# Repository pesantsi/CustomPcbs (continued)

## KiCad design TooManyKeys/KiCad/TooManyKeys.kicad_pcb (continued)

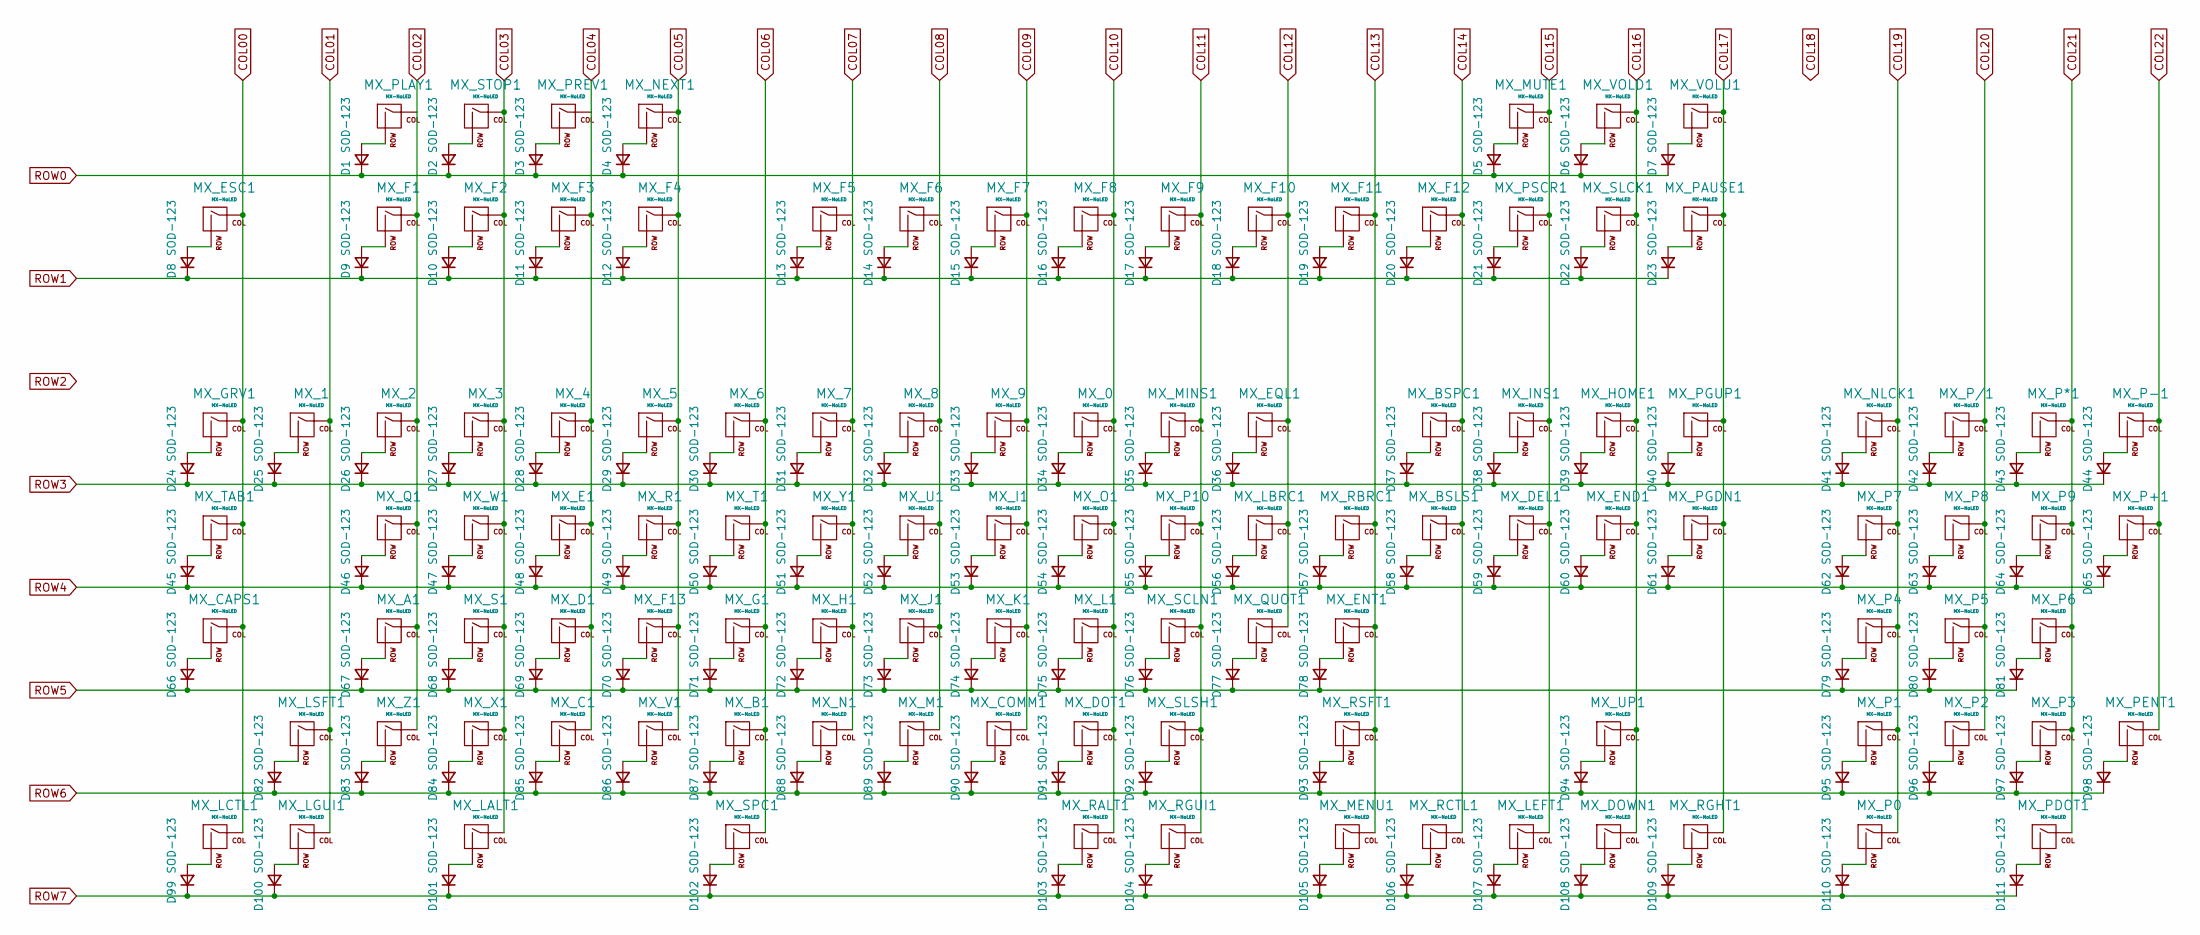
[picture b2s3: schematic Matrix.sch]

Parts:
D1, D2, D3, D4, D5, D6, D7, D8, D9, D10, D11, D12, D13, D14, D15, D16, D17, D18, D19, D20, D21, D22, D23, D24, D25, D26, D27, D28, D29, D30, D31, D32, D33, D34, D35, D36, D37, D38, D39, D40, D41, D42, D43, D44, D45, D46, D47, D48, D49, D50, D51, D52, D53, D54, D55, D56, D57, D58, D59, D60, D61, D62, D63, D64, D65, D66, D67, D68, D69, D70, D71, D72, D73, D74, D75, D76, D77, D78, D79, D80, D81, D82, D83, D84, D85, D86, D87, D88, D89, D90, D91, D92, D93, D94, D95, D96, D97, D98, D99, D100, D101, D102, D103, D104, D105, D106, D107, D108, D109, D110, D111: SOD-123; D_SOD-123
MX_0, MX_1, MX_2, MX_3, MX_4, MX_5, MX_6, MX_7, MX_8, MX_9: MX-NoLED; MXOnly-1U-NoLED
MX_A1: MX-NoLED; MXOnly-1U-NoLED
MX_B1: MX-NoLED; MXOnly-1U-NoLED
MX_BSLS1: MX-NoLED; MXOnly-1.5U-NoLED
MX_BSPC1: MX-NoLED; MXOnly-2U-NoLED
MX_C1: MX-NoLED; MXOnly-1U-NoLED
MX_CAPS1: MX-NoLED; MXOnly-1.75U-NoLED
MX_COMM1: MX-NoLED; MXOnly-1U-NoLED
MX_D1: MX-NoLED; MXOnly-1U-NoLED
MX_DEL1: MX-NoLED; MXOnly-1U-NoLED
MX_DOT1: MX-NoLED; MXOnly-1U-NoLED
MX_DOWN1: MX-NoLED; MXOnly-1U-NoLED
MX_E1: MX-NoLED; MXOnly-1U-NoLED
MX_END1: MX-NoLED; MXOnly-1U-NoLED
MX_ENT1: MX-NoLED; MXOnly-2.25U-NoLED
MX_EQL1: MX-NoLED; MXOnly-1U-NoLED
MX_ESC1: MX-NoLED; MXOnly-1U-NoLED
MX_F1, MX_F2, MX_F3, MX_F4, MX_F5, MX_F6, MX_F7, MX_F8, MX_F9, MX_F10, MX_F11, MX_F12, MX_F13: MX-NoLED; MXOnly-1U-NoLED
MX_G1: MX-NoLED; MXOnly-1U-NoLED
MX_GRV1: MX-NoLED; MXOnly-1U-NoLED
MX_H1: MX-NoLED; MXOnly-1U-NoLED
MX_HOME1: MX-NoLED; MXOnly-1U-NoLED
MX_I1: MX-NoLED; MXOnly-1U-NoLED
MX_INS1: MX-NoLED; MXOnly-1U-NoLED
MX_J1: MX-NoLED; MXOnly-1U-NoLED
MX_K1: MX-NoLED; MXOnly-1U-NoLED
MX_L1: MX-NoLED; MXOnly-1U-NoLED
MX_LALT1: MX-NoLED; MXOnly-1.25U-NoLED
MX_LBRC1: MX-NoLED; MXOnly-1U-NoLED
MX_LCTL1: MX-NoLED; MXOnly-1.25U-NoLED
MX_LEFT1: MX-NoLED; MXOnly-1U-NoLED
MX_LGUI1: MX-NoLED; MXOnly-1.25U-NoLED
MX_LSFT1: MX-NoLED; MXOnly-2.25U-NoLED
MX_M1: MX-NoLED; MXOnly-1U-NoLED
MX_MENU1: MX-NoLED; MXOnly-1.25U-NoLED
MX_MINS1: MX-NoLED; MXOnly-1U-NoLED
MX_MUTE1: MX-NoLED; MXOnly-1U-NoLED
MX_N1: MX-NoLED; MXOnly-1U-NoLED
MX_NEXT1: MX-NoLED; MXOnly-1U-NoLED
MX_NLCK1: MX-NoLED; MXOnly-1U-NoLED
MX_O1: MX-NoLED; MXOnly-1U-NoLED
MX_P0: MX-NoLED; MXOnly-2U-NoLED
MX_P1, MX_P2, MX_P3, MX_P4, MX_P5, MX_P6, MX_P7, MX_P8, MX_P9, MX_P10: MX-NoLED; MXOnly-1U-NoLED
MX_P*1: MX-NoLED; MXOnly-1U-NoLED
MX_P+1: MX-NoLED; MXOnly-2U-NoLED_Vertical
MX_P-1: MX-NoLED; MXOnly-1U-NoLED
MX_P/1: MX-NoLED; MXOnly-1U-NoLED
MX_PAUSE1: MX-NoLED; MXOnly-1U-NoLED
MX_PDOT1: MX-NoLED; MXOnly-1U-NoLED
MX_PENT1: MX-NoLED; MXOnly-2U-NoLED_Vertical
MX_PGDN1: MX-NoLED; MXOnly-1U-NoLED
MX_PGUP1: MX-NoLED; MXOnly-1U-NoLED
MX_PLAY1: MX-NoLED; MXOnly-1U-NoLED
MX_PREV1: MX-NoLED; MXOnly-1U-NoLED
MX_PSCR1: MX-NoLED; MXOnly-1U-NoLED
MX_Q1: MX-NoLED; MXOnly-1U-NoLED
MX_QUOT1: MX-NoLED; MXOnly-1U-NoLED
MX_R1: MX-NoLED; MXOnly-1U-NoLED
MX_RALT1: MX-NoLED; MXOnly-1.25U-NoLED
MX_RBRC1: MX-NoLED; MXOnly-1U-NoLED
MX_RCTL1: MX-NoLED; MXOnly-1.25U-NoLED
MX_RGHT1: MX-NoLED; MXOnly-1U-NoLED
MX_RGUI1: MX-NoLED; MXOnly-1.25U-NoLED
MX_RSFT1: MX-NoLED; MXOnly-2.75U-NoLED
MX_S1: MX-NoLED; MXOnly-1U-NoLED
MX_SCLN1: MX-NoLED; MXOnly-1U-NoLED
MX_SLCK1: MX-NoLED; MXOnly-1U-NoLED
MX_SLSH1: MX-NoLED; MXOnly-1U-NoLED
MX_SPC1: MX-NoLED; MXOnly-6.25U-NoLED
MX_STOP1: MX-NoLED; MXOnly-1U-NoLED
MX_T1: MX-NoLED; MXOnly-1U-NoLED
MX_TAB1: MX-NoLED; MXOnly-1.5U-NoLED
MX_U1: MX-NoLED; MXOnly-1U-NoLED
MX_UP1: MX-NoLED; MXOnly-1U-NoLED
MX_V1: MX-NoLED; MXOnly-1U-NoLED
MX_VOLD1: MX-NoLED; MXOnly-1U-NoLED
MX_VOLU1: MX-NoLED; MXOnly-1U-NoLED
MX_W1: MX-NoLED; MXOnly-1U-NoLED
MX_X1: MX-NoLED; MXOnly-1U-NoLED
MX_Y1: MX-NoLED; MXOnly-1U-NoLED
MX_Z1: MX-NoLED; MXOnly-1U-NoLED

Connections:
COL00: MX_CAPS1.1 (COL), MX_ESC1.1 (COL), MX_GRV1.1 (COL), MX_LCTL1.1 (COL), MX_TAB1.1 (COL); also elsewhere on the board
COL01: MX_1.1 (COL), MX_LGUI1.1 (COL), MX_LSFT1.1 (COL); also elsewhere on the board
COL02: MX_2.1 (COL), MX_A1.1 (COL), MX_F1.1 (COL), MX_PLAY1.1 (COL), MX_Q1.1 (COL), MX_Z1.1 (COL); also elsewhere on the board
COL03: MX_3.1 (COL), MX_F2.1 (COL), MX_LALT1.1 (COL), MX_S1.1 (COL), MX_STOP1.1 (COL), MX_W1.1 (COL), MX_X1.1 (COL); also elsewhere on the board
COL04: MX_4.1 (COL), MX_C1.1 (COL), MX_D1.1 (COL), MX_E1.1 (COL), MX_F3.1 (COL), MX_PREV1.1 (COL); also elsewhere on the board
COL05: MX_5.1 (COL), MX_F4.1 (COL), MX_F13.1 (COL), MX_NEXT1.1 (COL), MX_R1.1 (COL), MX_V1.1 (COL); also elsewhere on the board
COL06: MX_6.1 (COL), MX_B1.1 (COL), MX_G1.1 (COL), MX_SPC1.1 (COL), MX_T1.1 (COL); also elsewhere on the board
COL07: MX_7.1 (COL), MX_F5.1 (COL), MX_H1.1 (COL), MX_N1.1 (COL), MX_Y1.1 (COL); also elsewhere on the board
COL08: MX_8.1 (COL), MX_F6.1 (COL), MX_J1.1 (COL), MX_M1.1 (COL), MX_U1.1 (COL); also elsewhere on the board
COL09: MX_9.1 (COL), MX_COMM1.1 (COL), MX_F7.1 (COL), MX_I1.1 (COL), MX_K1.1 (COL); also elsewhere on the board
COL10: MX_0.1 (COL), MX_DOT1.1 (COL), MX_F8.1 (COL), MX_L1.1 (COL), MX_O1.1 (COL), MX_RALT1.1 (COL); also elsewhere on the board
COL11: MX_F9.1 (COL), MX_MINS1.1 (COL), MX_P10.1 (COL), MX_RGUI1.1 (COL), MX_SCLN1.1 (COL), MX_SLSH1.1 (COL); also elsewhere on the board
COL12: MX_EQL1.1 (COL), MX_F10.1 (COL), MX_LBRC1.1 (COL), MX_QUOT1.1 (COL); also elsewhere on the board
COL13: MX_ENT1.1 (COL), MX_F11.1 (COL), MX_MENU1.1 (COL), MX_RBRC1.1 (COL), MX_RSFT1.1 (COL); also elsewhere on the board
COL14: MX_BSLS1.1 (COL), MX_BSPC1.1 (COL), MX_F12.1 (COL), MX_RCTL1.1 (COL); also elsewhere on the board
COL15: MX_DEL1.1 (COL), MX_INS1.1 (COL), MX_LEFT1.1 (COL), MX_MUTE1.1 (COL), MX_PSCR1.1 (COL); also elsewhere on the board
COL16: MX_DOWN1.1 (COL), MX_END1.1 (COL), MX_HOME1.1 (COL), MX_SLCK1.1 (COL), MX_UP1.1 (COL), MX_VOLD1.1 (COL); also elsewhere on the board
COL17: MX_PAUSE1.1 (COL), MX_PGDN1.1 (COL), MX_PGUP1.1 (COL), MX_RGHT1.1 (COL), MX_VOLU1.1 (COL); also elsewhere on the board
COL19: MX_NLCK1.1 (COL), MX_P0.1 (COL), MX_P1.1 (COL), MX_P4.1 (COL), MX_P7.1 (COL); also elsewhere on the board
COL20: MX_P2.1 (COL), MX_P5.1 (COL), MX_P8.1 (COL), MX_P/1.1 (COL); also elsewhere on the board
COL21: MX_P3.1 (COL), MX_P6.1 (COL), MX_P9.1 (COL), MX_P*1.1 (COL), MX_PDOT1.1 (COL); also elsewhere on the board
COL22: MX_P+1.1 (COL), MX_P-1.1 (COL), MX_PENT1.1 (COL); also elsewhere on the board
unnamed: D1.2 (A), MX_PLAY1.2 (ROW)
unnamed: D2.2 (A), MX_STOP1.2 (ROW)
unnamed: D3.2 (A), MX_PREV1.2 (ROW)
unnamed: D4.2 (A), MX_NEXT1.2 (ROW)
unnamed: D5.2 (A), MX_MUTE1.2 (ROW)
unnamed: D6.2 (A), MX_VOLD1.2 (ROW)
unnamed: D7.2 (A), MX_VOLU1.2 (ROW)
unnamed: D8.2 (A), MX_ESC1.2 (ROW)
unnamed: D9.2 (A), MX_F1.2 (ROW)
unnamed: D10.2 (A), MX_F2.2 (ROW)
unnamed: D11.2 (A), MX_F3.2 (ROW)
unnamed: D12.2 (A), MX_F4.2 (ROW)
unnamed: D13.2 (A), MX_F5.2 (ROW)
unnamed: D14.2 (A), MX_F6.2 (ROW)
unnamed: D15.2 (A), MX_F7.2 (ROW)
unnamed: D16.2 (A), MX_F8.2 (ROW)
unnamed: D17.2 (A), MX_F9.2 (ROW)
unnamed: D18.2 (A), MX_F10.2 (ROW)
unnamed: D19.2 (A), MX_F11.2 (ROW)
unnamed: D20.2 (A), MX_F12.2 (ROW)
unnamed: D21.2 (A), MX_PSCR1.2 (ROW)
unnamed: D22.2 (A), MX_SLCK1.2 (ROW)
unnamed: D23.2 (A), MX_PAUSE1.2 (ROW)
unnamed: D24.2 (A), MX_GRV1.2 (ROW)
unnamed: D25.2 (A), MX_1.2 (ROW)
unnamed: D26.2 (A), MX_2.2 (ROW)
unnamed: D27.2 (A), MX_3.2 (ROW)
unnamed: D28.2 (A), MX_4.2 (ROW)
unnamed: D29.2 (A), MX_5.2 (ROW)
unnamed: D30.2 (A), MX_6.2 (ROW)
unnamed: D31.2 (A), MX_7.2 (ROW)
unnamed: D32.2 (A), MX_8.2 (ROW)
unnamed: D33.2 (A), MX_9.2 (ROW)
unnamed: D34.2 (A), MX_0.2 (ROW)
unnamed: D35.2 (A), MX_MINS1.2 (ROW)
unnamed: D36.2 (A), MX_EQL1.2 (ROW)
unnamed: D37.2 (A), MX_BSPC1.2 (ROW)
unnamed: D38.2 (A), MX_INS1.2 (ROW)
unnamed: D39.2 (A), MX_HOME1.2 (ROW)
unnamed: D40.2 (A), MX_PGUP1.2 (ROW)
unnamed: D41.2 (A), MX_NLCK1.2 (ROW)
unnamed: D42.2 (A), MX_P/1.2 (ROW)
unnamed: D43.2 (A), MX_P*1.2 (ROW)
unnamed: D44.2 (A), MX_P-1.2 (ROW)
unnamed: D45.2 (A), MX_TAB1.2 (ROW)
unnamed: D46.2 (A), MX_Q1.2 (ROW)
unnamed: D47.2 (A), MX_W1.2 (ROW)
unnamed: D48.2 (A), MX_E1.2 (ROW)
unnamed: D49.2 (A), MX_R1.2 (ROW)
unnamed: D50.2 (A), MX_T1.2 (ROW)
unnamed: D51.2 (A), MX_Y1.2 (ROW)
unnamed: D52.2 (A), MX_U1.2 (ROW)
unnamed: D53.2 (A), MX_I1.2 (ROW)
unnamed: D54.2 (A), MX_O1.2 (ROW)
unnamed: D55.2 (A), MX_P10.2 (ROW)
unnamed: D56.2 (A), MX_LBRC1.2 (ROW)
unnamed: D57.2 (A), MX_RBRC1.2 (ROW)
unnamed: D58.2 (A), MX_BSLS1.2 (ROW)
unnamed: D59.2 (A), MX_DEL1.2 (ROW)
unnamed: D60.2 (A), MX_END1.2 (ROW)
unnamed: D61.2 (A), MX_PGDN1.2 (ROW)
unnamed: D62.2 (A), MX_P7.2 (ROW)
unnamed: D63.2 (A), MX_P8.2 (ROW)
unnamed: D64.2 (A), MX_P9.2 (ROW)
unnamed: D65.2 (A), MX_P+1.2 (ROW)
unnamed: D66.2 (A), MX_CAPS1.2 (ROW)
unnamed: D67.2 (A), MX_A1.2 (ROW)
unnamed: D68.2 (A), MX_S1.2 (ROW)
unnamed: D69.2 (A), MX_D1.2 (ROW)
unnamed: D70.2 (A), MX_F13.2 (ROW)
unnamed: D71.2 (A), MX_G1.2 (ROW)
unnamed: D72.2 (A), MX_H1.2 (ROW)
unnamed: D73.2 (A), MX_J1.2 (ROW)
unnamed: D74.2 (A), MX_K1.2 (ROW)
unnamed: D75.2 (A), MX_L1.2 (ROW)
unnamed: D76.2 (A), MX_SCLN1.2 (ROW)
unnamed: D77.2 (A), MX_QUOT1.2 (ROW)
unnamed: D78.2 (A), MX_ENT1.2 (ROW)
unnamed: D79.2 (A), MX_P4.2 (ROW)
unnamed: D80.2 (A), MX_P5.2 (ROW)
unnamed: D81.2 (A), MX_P6.2 (ROW)
unnamed: D82.2 (A), MX_LSFT1.2 (ROW)
unnamed: D83.2 (A), MX_Z1.2 (ROW)
unnamed: D84.2 (A), MX_X1.2 (ROW)
unnamed: D85.2 (A), MX_C1.2 (ROW)
unnamed: D86.2 (A), MX_V1.2 (ROW)
unnamed: D87.2 (A), MX_B1.2 (ROW)
unnamed: D88.2 (A), MX_N1.2 (ROW)
unnamed: D89.2 (A), MX_M1.2 (ROW)
unnamed: D90.2 (A), MX_COMM1.2 (ROW)
unnamed: D91.2 (A), MX_DOT1.2 (ROW)
unnamed: D92.2 (A), MX_SLSH1.2 (ROW)
unnamed: D93.2 (A), MX_RSFT1.2 (ROW)
unnamed: D94.2 (A), MX_UP1.2 (ROW)
unnamed: D95.2 (A), MX_P1.2 (ROW)
unnamed: D96.2 (A), MX_P2.2 (ROW)
unnamed: D97.2 (A), MX_P3.2 (ROW)
unnamed: D98.2 (A), MX_PENT1.2 (ROW)
unnamed: D99.2 (A), MX_LCTL1.2 (ROW)
unnamed: D100.2 (A), MX_LGUI1.2 (ROW)
unnamed: D101.2 (A), MX_LALT1.2 (ROW)
unnamed: D102.2 (A), MX_SPC1.2 (ROW)
unnamed: D103.2 (A), MX_RALT1.2 (ROW)
unnamed: D104.2 (A), MX_RGUI1.2 (ROW)
unnamed: D105.2 (A), MX_MENU1.2 (ROW)
unnamed: D106.2 (A), MX_RCTL1.2 (ROW)
unnamed: D107.2 (A), MX_LEFT1.2 (ROW)
unnamed: D108.2 (A), MX_DOWN1.2 (ROW)
unnamed: D109.2 (A), MX_RGHT1.2 (ROW)
unnamed: D110.2 (A), MX_P0.2 (ROW)
unnamed: D111.2 (A), MX_PDOT1.2 (ROW)
ROW0: D1.1 (K), D2.1 (K), D3.1 (K), D4.1 (K), D5.1 (K), D6.1 (K), D7.1 (K); also elsewhere on the board
ROW1: D8.1 (K), D9.1 (K), D10.1 (K), D11.1 (K), D12.1 (K), D13.1 (K), D14.1 (K), D15.1 (K), D16.1 (K), D17.1 (K), D18.1 (K), D19.1 (K), D20.1 (K), D21.1 (K), D22.1 (K), D23.1 (K); also elsewhere on the board
ROW3: D24.1 (K), D25.1 (K), D26.1 (K), D27.1 (K), D28.1 (K), D29.1 (K), D30.1 (K), D31.1 (K), D32.1 (K), D33.1 (K), D34.1 (K), D35.1 (K), D36.1 (K), D37.1 (K), D38.1 (K), D39.1 (K), D40.1 (K), D41.1 (K), D42.1 (K), D43.1 (K), D44.1 (K); also elsewhere on the board
ROW4: D45.1 (K), D46.1 (K), D47.1 (K), D48.1 (K), D49.1 (K), D50.1 (K), D51.1 (K), D52.1 (K), D53.1 (K), D54.1 (K), D55.1 (K), D56.1 (K), D57.1 (K), D58.1 (K), D59.1 (K), D60.1 (K), D61.1 (K), D62.1 (K), D63.1 (K), D64.1 (K), D65.1 (K); also elsewhere on the board
ROW5: D66.1 (K), D67.1 (K), D68.1 (K), D69.1 (K), D70.1 (K), D71.1 (K), D72.1 (K), D73.1 (K), D74.1 (K), D75.1 (K), D76.1 (K), D77.1 (K), D78.1 (K), D79.1 (K), D80.1 (K), D81.1 (K); also elsewhere on the board
ROW6: D82.1 (K), D83.1 (K), D84.1 (K), D85.1 (K), D86.1 (K), D87.1 (K), D88.1 (K), D89.1 (K), D90.1 (K), D91.1 (K), D92.1 (K), D93.1 (K), D94.1 (K), D95.1 (K), D96.1 (K), D97.1 (K), D98.1 (K); also elsewhere on the board
ROW7: D99.1 (K), D100.1 (K), D101.1 (K), D102.1 (K), D103.1 (K), D104.1 (K), D105.1 (K), D106.1 (K), D107.1 (K), D108.1 (K), D109.1 (K), D110.1 (K), D111.1 (K); also elsewhere on the board

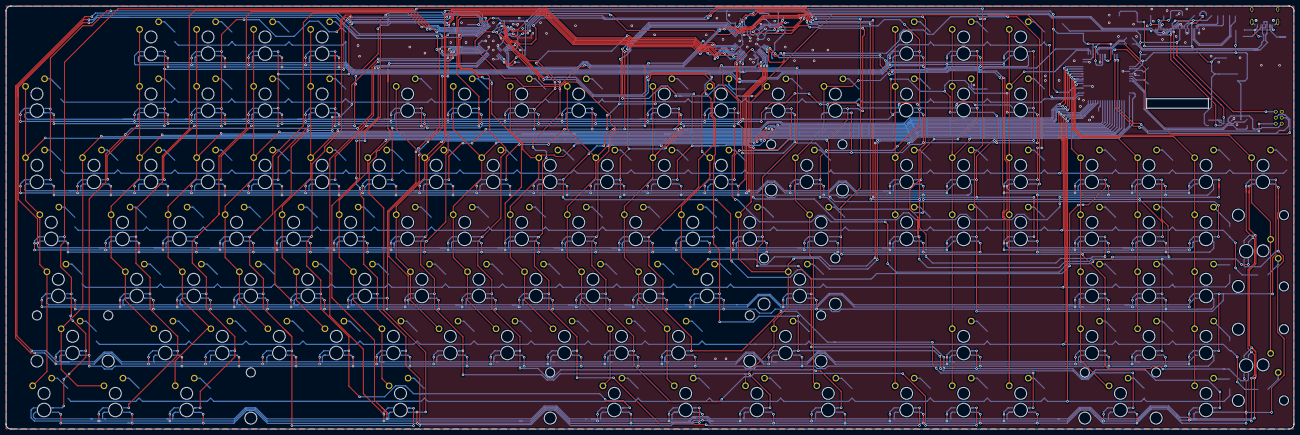
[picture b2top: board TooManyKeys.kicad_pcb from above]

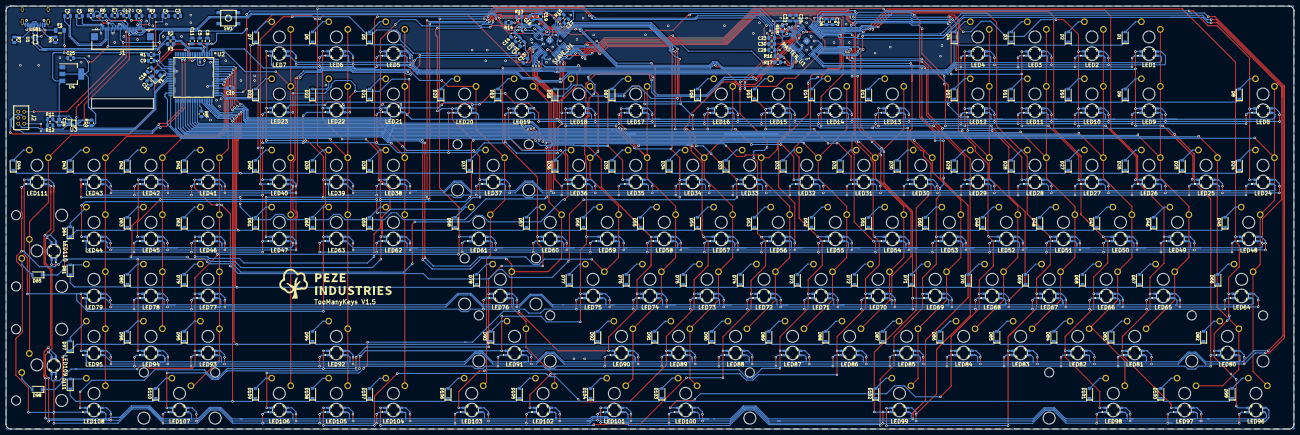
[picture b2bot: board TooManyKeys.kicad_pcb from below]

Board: 2 copper layers, 430.2 x 141.3 mm, 393 parts (282 on the bottom side), 233 nets.

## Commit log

2020-03-02 Init pcb's
2020-03-02 adding sub modules
2020-03-02 add libs
2020-03-03 adding cache
2020-03-05 Adding Matrix Schema
2020-03-05 adding matrix and adafruit
2020-03-06 Removed submodule Voyager104
2020-03-06 Adding Voyager104
2020-03-09 Modify Voyager
2020-03-11 adding kbfirmware config
2020-03-30 Adding TooManykeys
2020-03-30 First draft Sch
2020-03-31 Matrix sch finished
2020-04-01 adding voltage controller and i2c controller
2020-04-01 finish work on matrix
2020-04-03 adding IS31FL3733-TQ to led sch
2020-04-10 led work
2020-12-21 Adding led matrix
2020-12-21 V1 Schematics
2020-12-21 WIP pcb
2020-12-22 WIP pcb 2
2020-12-24 changes made to schematics following upwork
2020-12-29 Final Schematic version, starting work on pcb
2021-01-01 V1 New Led Positions
2021-01-01 Led alignment
2021-01-02 Partial Routing
2021-01-13 New footprint, pcb key matrix completed
2021-01-17 Before changing to new led and moving mcu caps and usb resistors
2021-01-17 New led symbols and footprint
2021-01-18 RBG Led replaced
2021-01-20 Updated RGB Led footprint and more routing
2021-01-22 Almost done, some routing left
2021-01-27 switch plate
2021-01-28 plate and board diagrams
2021-01-28 Folder Updates
2021-01-28 Initial commit for driver
2021-01-29 After extensive work
2021-01-29 Updated Logo
2021-01-30 Missing F10 key
2021-02-01 switch plate diagrams
2021-02-01 Final Version of Schematic and PCB
2021-02-01 Gerber Files
2021-02-02 Diagrams V2 and gerber files updated
2021-02-02 Working version of Driver Update
2021-02-05 Update files for manufacturing
2021-02-05 Final version of switch plate
2021-02-05 useless file
2021-02-24 Adding PCBWay pics
2021-04-23 Update LED footprint, missing SMT assembly property
2021-05-14 Flip Led Footprint
    Added version 1.5 to pcb
    Added version 1.2 to sch
    Added proper Level Shifter to BOM
2021-05-14 Finished work on new led footprint, need to double check
2021-05-17 Set Led footprint text position
    Renaming items in footprint library
2021-05-17 Updating pcb with IS31FL3733-TQLS4 footprint
2021-05-18 All designator are properly placed
2021-05-19 Missing Shift key + routing
2021-05-19 Missing Shift key + routing save
2021-05-19 + Routing
2021-05-20 Final routing + properly saved 3 pins footprint
2021-05-20 Final fill ground plane
2021-05-20 V1.5 Gerber files
2021-05-20 V1.5 Position File
2021-06-26 Changes following contractor review( ressources / Schematic Review.docx )
2021-07-21 Creating Proto for TooManyKeys
2021-07-21 Routing finished
2021-07-22 Final touches on Proto and added a missing capacitor
2021-07-22 repair file sent to micro repair
2021-07-22 routing fixes, new gerber files
2021-07-22 updated gerber files + latest bom
2021-07-22 Adding position fie
2021-07-23 updated gerber files
2022-01-21 NextPCB Bom
2022-06-23 Bump Newtonsoft.Json in /TooManyKeys/Driver/Driver.Nuget
    Bumps [Newtonsoft.Json](https://github.com/JamesNK/Newtonsoft.Json) from 12.0.3 to 13.0.1.
    - [Release notes](https://github.com/JamesNK/Newtonsoft.Json/releases)
    - [Commits](https://github.com/JamesNK/Newtonsoft.Json/compare/12.0.3...13.0.1)
    ---
    updated-dependencies:
    - dependency-name: Newtonsoft.Json
2022-06-23 Bump Newtonsoft.Json in /TooManyKeys/Driver/Driver.Updater
    Bumps [Newtonsoft.Json](https://github.com/JamesNK/Newtonsoft.Json) from 12.0.3 to 13.0.1.
    - [Release notes](https://github.com/JamesNK/Newtonsoft.Json/releases)
    - [Commits](https://github.com/JamesNK/Newtonsoft.Json/compare/12.0.3...13.0.1)
    ---
    updated-dependencies:
    - dependency-name: Newtonsoft.Json
2022-10-11 Bump NuGet.Protocol in /TooManyKeys/Driver/Driver.Nuget
    Bumps [NuGet.Protocol](https://github.com/NuGet/NuGet.Client) from 5.8.1 to 5.9.3.
    - [Release notes](https://github.com/NuGet/NuGet.Client/releases)
    - [Commits](https://github.com/NuGet/NuGet.Client/commits)
    ---
    updated-dependencies:
    - dependency-name: NuGet.Protocol
2022-12-08 Bump Newtonsoft.Json in /TooManyKeys/Driver/Driver.Nuget
    Bumps [Newtonsoft.Json](https://github.com/JamesNK/Newtonsoft.Json) from 12.0.3 to 13.0.2.
    - [Release notes](https://github.com/JamesNK/Newtonsoft.Json/releases)
    - [Commits](https://github.com/JamesNK/Newtonsoft.Json/compare/12.0.3...13.0.2)
    ---
    updated-dependencies:
    - dependency-name: Newtonsoft.Json
2022-12-08 Bump Newtonsoft.Json in /TooManyKeys/Driver/Driver.Updater
    Bumps [Newtonsoft.Json](https://github.com/JamesNK/Newtonsoft.Json) from 12.0.3 to 13.0.2.
    - [Release notes](https://github.com/JamesNK/Newtonsoft.Json/releases)
    - [Commits](https://github.com/JamesNK/Newtonsoft.Json/compare/12.0.3...13.0.2)
    ---
    updated-dependencies:
    - dependency-name: Newtonsoft.Json
